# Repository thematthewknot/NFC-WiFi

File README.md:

# What is NFC-WiFi?
It is a NFC reader with WiFi!  
This project joins a NFC reader(PN532) to a WeMos D1 Mini to allow for WiFi access.  
What can you do with this?
* Toggle a IFTTT event with a NFC tag
* Integrate into home automation systems
* Send notification when scanned
* And much more

# Getting started
Go check out the getting started [tutorials](https://www.mattvarian.com/nfc-wifi)

# Videos 
[Initial setup](https://youtu.be/GJwHEKRzi4o)

[Opening Front Door](https://www.youtube.com/watch?v=mKFkm8zK5ho)

# Where do I get one?

They are now for sale on my tindie: [Get yours here](https://www.tindie.com/products/thematthewknot/nfc-wifi-board/)

# Hardware used
* PN532 Board
* WeMos D1 Mini 4M
* custom PCB to join the two with addressable RGB LED
* 3D printed Enclosure

# Pinout Notes
## Led (APA102)
* data - 5
* clock - 4

## D1 Mini (WeMos 4M)
* sck - 16 
* miso - 14
* mosi - 12
* ss - 13

# Enclosure 
The enclosure is 1.8in x 1.85in x 0.8in(46mm x 47mm x 20mm) 3D printed with PETG so should hold up to outdoors to some extent however if it's going to be outdoors you'll want to seal up the hole where the USB connects.  

There are also some diviots to ease in mounting via screws, or you can use double sided tape to attach it to a surface.  

There is a lid that can slide off to allow you to remove the boards from inside. The hole is designed for the USB cable I send with board/enclosures when purchased but should fit most micro-USB cables.  

# Initial setup links

[IFTTT webhooks](https://ifttt.com/maker_webhooks)
Click Connect
Then Click Documentation to get your key

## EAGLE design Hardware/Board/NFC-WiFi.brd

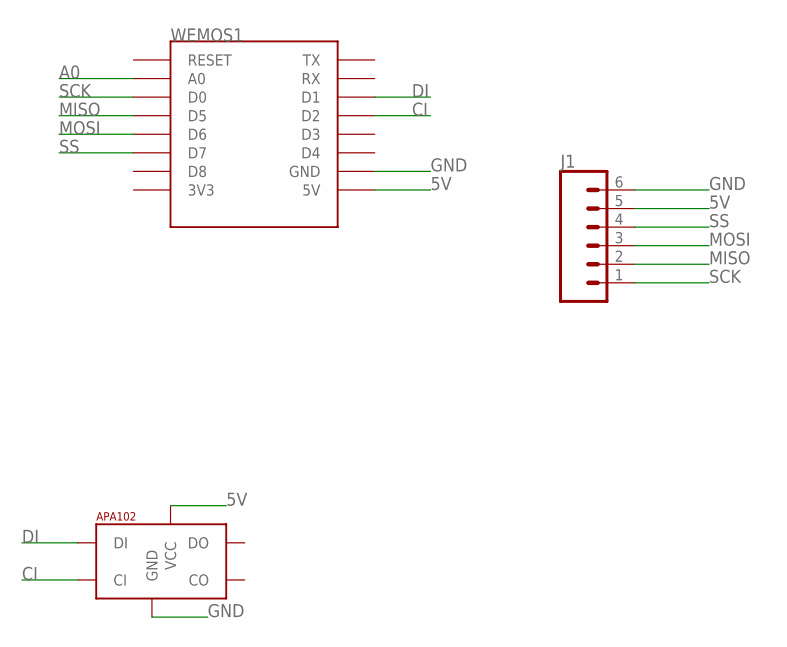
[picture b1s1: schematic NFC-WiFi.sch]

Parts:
J1: CONN_06SILK_FEMALE_PTH; 1X06
U$1: APA1025050; APA102_5050
WEMOS1: WEMOS-D1-MINI

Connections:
5V: J1.5, U$1.1 (VCC), WEMOS1.5V
A0: WEMOS1.A0
CI: U$1.5 (CI), WEMOS1.D2
DI: U$1.4 (DI), WEMOS1.D1
GND: J1.6, U$1.6 (GND), WEMOS1.GND
MISO: J1.2, WEMOS1.D5
MOSI: J1.3, WEMOS1.D6
SCK: J1.1, WEMOS1.D0
SS: J1.4, WEMOS1.D7

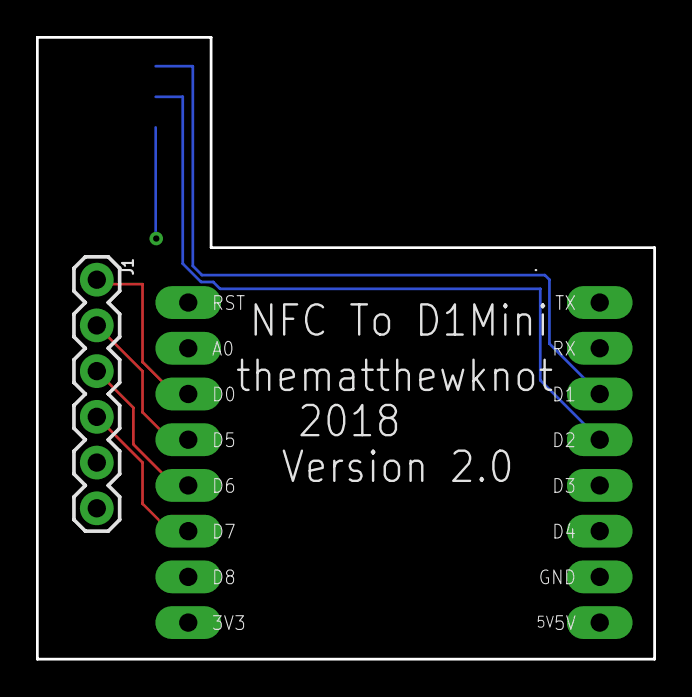
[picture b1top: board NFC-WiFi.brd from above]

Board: 2 copper layers, 34.3 x 34.5 mm, 3 parts (1 on the bottom side), 8 nets.

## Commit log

2019-03-19 Initial commit
    This code is just a basic program to test the LED and NFC , it does not yet integrate the WiFi.
2019-03-19 First commit
    These are the hardware files.
2019-03-19 fixed typo
    Fixed bullet points
2019-03-19 cleaned up pinout
    removed hardware pins to just have arduino pins
2019-03-19 added photo
2019-03-20 Updated webserver
    Working towards what the webserver will end up looking like
2019-03-20 Set theme jekyll-theme-midnight
2019-03-21 Added enclosure info
    added photo of enclosure
2019-03-21 typo
2019-03-21 formating
2019-03-24 Not yet working`
    Not working at all, but getting closer wanted to commit before i misplaced this.
2019-03-24 writing to flash
    Storing tag info and url to flash to persist after restart
2019-03-24 dont need bin file
2019-03-25 Added URL get request
    Need to clean up webpage and make it update dynamically still.
2019-03-25 Fixed webpage
    Webpage now shows uid/url, also now tracks size of uid/url
2019-03-26 clean up
    cleanup
2019-03-27 removed eeprom, started using fs.h
    removed eeprom and started using filesystem, way better.
2019-03-27 cleaned up stuff
    removed some extra functions web ui slightly better
2019-03-28 working on fixing https
    still working on it
2019-03-28 Fixed https
    Working now, uses SSL thanks to https://medium.com/@dfa_31434/doing-ssl-requests-on-esp8266-correctly-c1f60ad46f5e?fbclid=IwAR2SZxSkQQS_qBuUhRQ806xn1GtZLJolx8lyZoX5gAU_4rNSJrxNTAY7MwM
2019-03-29 tons of changes
    big shout out to hfuller for letting me steal tons of code, this is just being uploaded to save it incase pc dies, still in progress
2019-03-29 More changes
    Cleaning up functions
2019-03-29 Fixed performance issue
    Fixed performance issue
2019-03-30 Working copy, Almost there
    Working, just some cleaning up left
2019-03-30 https is broke
    no idea whats up, maybe my environment
2019-03-30 fixed https
    Needed to go back to ESP8266WiFi v2.4.2 that fixed everything.
2019-03-31 Sorta working
    https calls works sometimes, but not consistently http calls doesn't appear to work at all
2019-04-03 fixed http
    Added http handler to useURL
2019-04-03 fixed http, also reads cert numbers
2019-04-05 having random heap overflow issues with bearssl
    Not sure why, trying different ways to get it to play nice nothing working so far. Added a input for timezone to the setup page on the webpage.
2019-04-05 fixed small thing
    cert file uploader
2019-04-05 removed unneeded include
2019-04-05 trying something ignore this
2019-04-05 back to where was before
2019-04-07 ifttt working
    Finally.
2019-04-07 added ifttt link
2019-04-07 Done
    Well not done, but working well and ready to ship.
2019-04-23 working towards MQTT
    Starting to get stuff in place for MQTT support, webpage part nearly done.
2019-04-25 mqtt working
    MQTT working, passes along UID, need to clean up webpage formatting and test with username/pass.
2019-04-25 mqtt work
    added username/password/port to mqtt setup, turned led yellow when in webpage setup mode.
2019-05-04 MQTT Working
    Added MQTT support tested w/ user/pw
2019-05-06 updated order site
2019-08-04 Moved away from SPIFFS to LittleFS
    fixed a few issues, moved to use LittleFS

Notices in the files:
Hardware/Board/NFC-WiFi.brd:
GPL3
parts and their libraries:
SparkFun-Connectors: Licensing: Creative Commons ShareAlike 4.0 International - https://creativecommons.org/licenses/by-sa/4.0
